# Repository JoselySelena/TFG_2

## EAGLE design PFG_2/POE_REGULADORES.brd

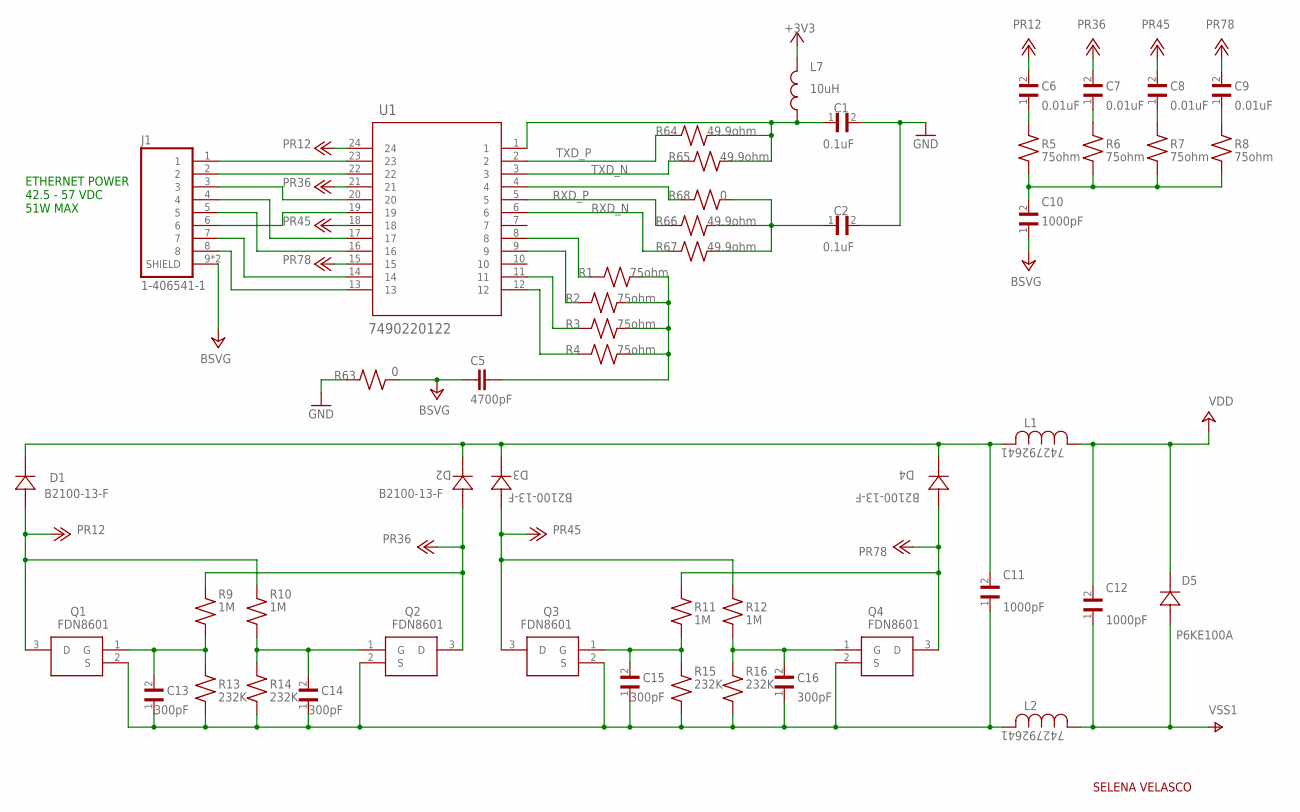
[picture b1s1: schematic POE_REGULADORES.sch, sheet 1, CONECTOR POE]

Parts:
C1, C2: 0.1uF; CAPC3316X98N
C5: 4700pF; C4532
C6, C7, C8, C9: 0.01uF; CAPC3316X98N
C10: 1000pF; CAPC4520X150N
C11, C12: 1000pF; CAPC3316X98N
C13, C14, C15, C16: 300pF; CAPC3316X98N
D1, D2, D3, D4: B2100-13-F; SMB_DIO
D5: P6KE100A; P6KESERIES_LTF
J1: 1-406541-1; CONN_1-406541-1
L1, L2: 742792641; IND_742792641_WRE
L7: 10uH; INDM3225X210N
Q1, Q2, Q3, Q4: FDN8601; SOT95P251X112-3N
R1, R2, R3, R4, R5, R6, R7, R8: 75ohm; RESC3116X65N
R9, R10, R11, R12: 1M; RESC3116X65N
R13, R14, R15, R16: 232K; RESC3116X65N
R63, R68: 0; RESC3116X65N
R64, R65, R66, R67: 49.9ohm; RESC3116X65N
U1: 7490220122; 7490220122_WRE

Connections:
+3V3: L7.2; also elsewhere on the board
BSVG: C5.1, C10.1, J1.9 (SHIELD), J1.10 (SHIELD), R63.1
GND: C1.2, C2.2, R63.2; also elsewhere on the board
unnamed: J1.1, U1.23
unnamed: J1.2, U1.22
unnamed: J1.3, U1.20
unnamed: J1.4, U1.17
unnamed: J1.5, U1.16
unnamed: J1.6, U1.19
unnamed: J1.7, U1.14
unnamed: J1.8, U1.13
unnamed: C14.2, Q2.1 (G), R10.1, R14.2
unnamed: C6.1, R5.2
unnamed: C7.1, R6.2
unnamed: C8.1, R7.2
unnamed: C9.1, R8.2
unnamed: C10.2, R5.1, R6.1, R7.1, R8.1
unnamed: R1.1, U1.8
unnamed: C5.2, R1.2, R2.2, R3.2, R4.2
unnamed: R2.1, U1.9
unnamed: R3.1, U1.11
unnamed: R4.1, U1.12
unnamed: C13.2, Q1.1 (G), R9.1, R13.2
unnamed: C15.2, Q3.1 (G), R11.1, R15.2
unnamed: C16.2, Q4.1 (G), R12.1, R16.2
unnamed: C11.2, D1.1, D2.1, D3.1, D4.1, L1.2
unnamed: C11.1, C13.1, C14.1, C15.1, C16.1, L2.2, Q1.2 (S), Q2.2 (S), Q3.2 (S), Q4.2 (S), R13.1, R14.1, R15.1, R16.1
unnamed: R68.1, U1.4
unnamed: C2.1, R66.2, R67.2, R68.2
PR12: C6.2, D1.2, Q1.3 (D), R10.2, U1.24
PR36: C7.2, D2.2, Q2.3 (D), R9.2, U1.21
PR45: C8.2, D3.2, Q3.3 (D), R12.2, U1.18
PR78: C9.2, D4.2, Q4.3 (D), R11.2, U1.15
RXD_N: R67.1, U1.6; also elsewhere on the board
RXD_P: R66.1, U1.5; also elsewhere on the board
TXD_CT: C1.1, L7.1, R64.2, R65.2, U1.1
TXD_N: R65.1, U1.3; also elsewhere on the board
TXD_P: R64.1, U1.2; also elsewhere on the board
VDD: C12.2, D5.1, L1.1; also elsewhere on the board
VSS1: C12.1, D5.2, L2.1; also elsewhere on the board

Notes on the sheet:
ETHERNET POWER 42.5 - 57 VDC 51W MAX
SELENA VELASCO

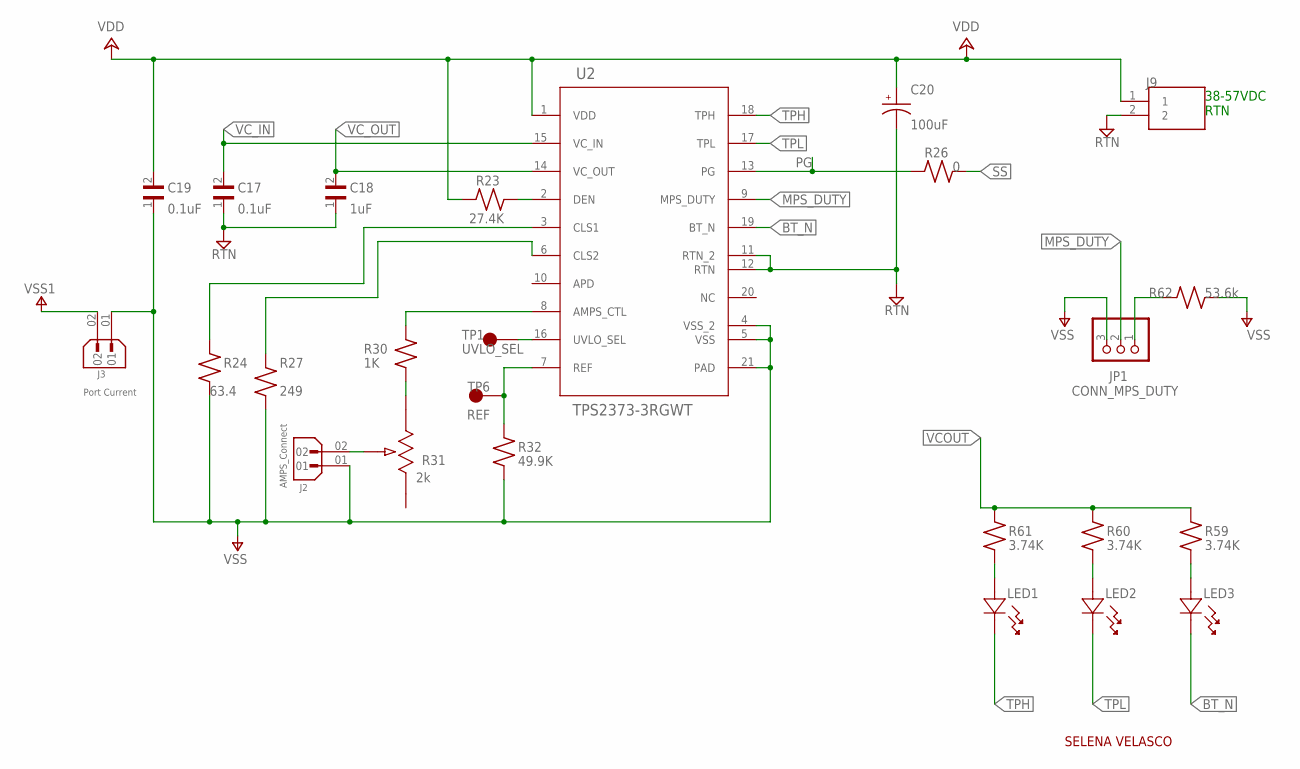
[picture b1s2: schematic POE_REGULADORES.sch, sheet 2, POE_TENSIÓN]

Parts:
C17, C19: 0.1uF; CAPC3316X98N
C18: 1uF; CAPC3316X98N
C20: 100uF; CAP_EEEFK1J470P
J2: AMPS_Connect; WURTH_61300211121
J3: Port Current; WURTH_61300211121
J9: TB001-500-02BE; CUI_TB001-500-02BE
JP1: CONN_MPS_DUTY; 1X03
LED1, LED2, LED3: BL-BGE1V1; BL-BGE1V1_AMB
R23: 27.4K; RESC3116X65N
R24: 63.4; RESC3116X65N
R26: 0; RESC3116X65N
R27: 249; RESC3116X65N
R30: 1K; RESC3116X65N
R31: 2k; POT_3386P
R32: 49.9K; RESC3116X65N
R59, R60, R61: 3.74K; RESC3116X65N
R62: 53.6k; RESC3116X65N
TP1: UVLO_SEL; KEYSTONE_5019
TP6: REF; KEYSTONE_5019
U2: TPS2373-3RGWT; RGW0020B

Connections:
BT_N: LED3.1, U2.19 (BT_N)
MPS_DUTY: JP1.2, U2.9 (MPS_DUTY)
unnamed: LED3.2, R59.1
unnamed: R24.2, U2.3 (CLS1)
unnamed: R27.2, U2.6 (CLS2)
unnamed: R32.2, TP6.TP, U2.7 (REF)
unnamed: R30.1, R31.3
unnamed: J2.02, R31.2
unnamed: R23.2, U2.2 (DEN)
unnamed: R30.2, U2.8 (AMPS_CTL)
unnamed: TP1.TP, U2.16 (UVLO_SEL)
unnamed: JP1.1, R62.2
unnamed: LED1.2, R61.1
unnamed: LED2.2, R60.1
PG: R26.1, U2.13 (PG); also elsewhere on the board
RTN: C17.1, C18.1, C20.2, J9.2, U2.11 (RTN_2), U2.12 (RTN); also elsewhere on the board
SS: R26.2; also elsewhere on the board
TPH: LED1.1, U2.18 (TPH)
TPL: LED2.1, U2.17 (TPL)
VCOUT: R59.2, R60.2, R61.2
VC_IN: C17.2, U2.15 (VC_IN)
VC_OUT: C18.2, U2.14 (VC_OUT)
VDD: C19.2, C20.1, J9.1, R23.1, U2.1 (VDD); also elsewhere on the board
VSS: C19.1, J2.01, J3.01, JP1.3, R24.1, R27.1, R32.1, R62.1, U2.4 (VSS_2), U2.5 (VSS), U2.21 (PAD)
VSS1: J3.02; also elsewhere on the board

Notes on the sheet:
SELENA VELASCO
38-57VDC RTN

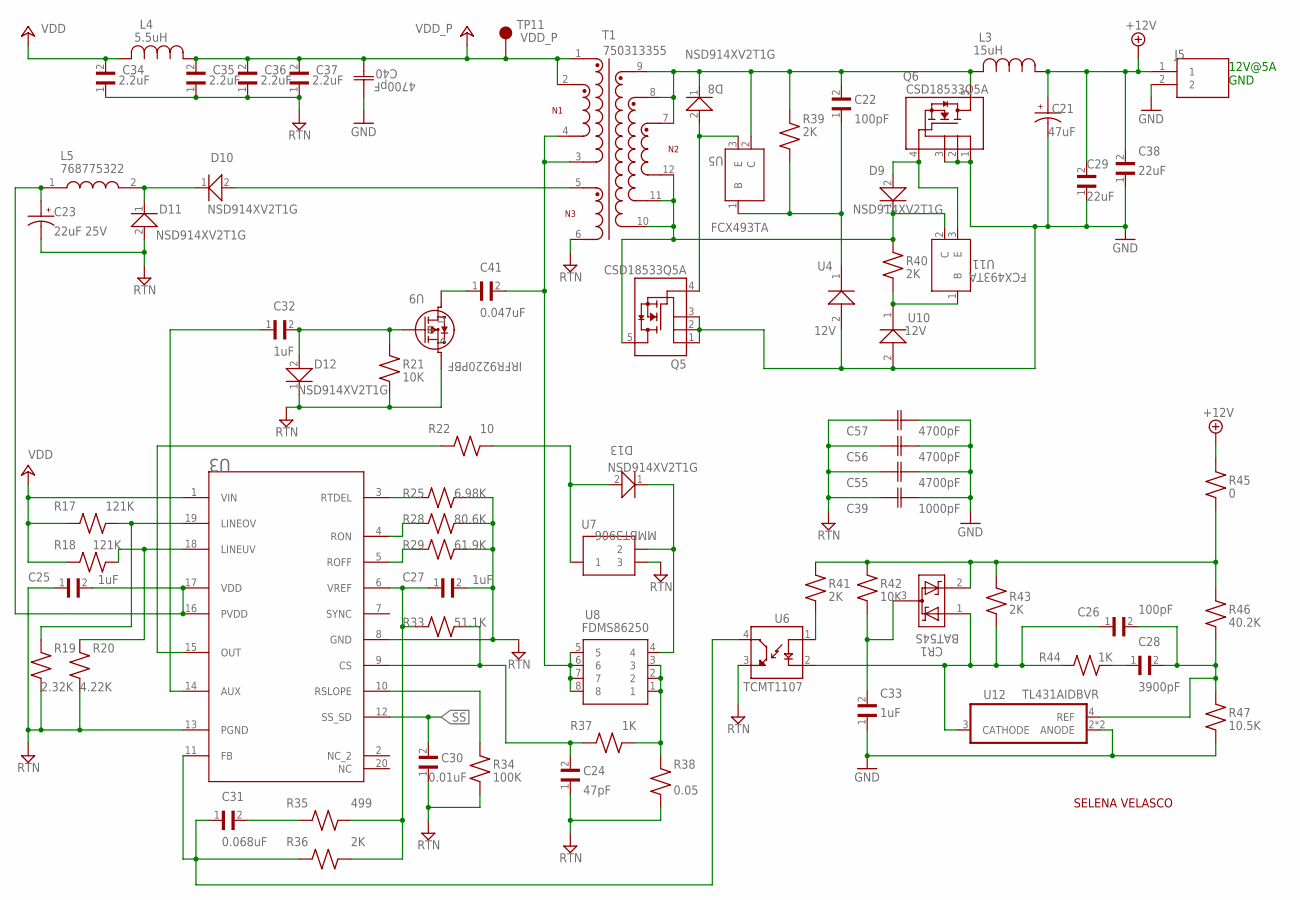
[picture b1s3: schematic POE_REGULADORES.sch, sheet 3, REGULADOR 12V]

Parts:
C21: 47uF; CAP_EEEFK1C470P
C22, C26: 100pF; CAPC3316X98N
C23: 22uF 25V; CAP_EEEFK1E220R
C24: 47pF; CAPC3316X98N
C25, C27, C32, C33: 1uF; CAPC3316X98N
C28: 3900pF; CAPC3316X98N
C29, C38: 22uF; CAPC3316X98N
C30: 0.01uF; CAPC3316X98N
C31: 0.068uF; CAPC3316X98N
C34, C35, C36, C37: 2.2uF; CAPC3316X98N
C39: 1000pF; CAP_1812_AVX
C40, C55, C56, C57: 4700pF; CAP_1812_AVX
C41: 0.047uF; CAPC3316X98N
CR1: BAT54S; SOT-23_TO-236_DTC
D8, D9, D10, D11, D12, D13: NSD914XV2T1G; SOD-523_0P9X1P3_ONS
J5: TB001-500-02BE; CUI_TB001-500-02BE
L3: 15uH; IND_1890_2-WE-HCI_WRE
L4: 5.5uH; IND_1050-WE-HCI_WRE
L5: 768775322
Q5, Q6: CSD18533Q5A; TRANS_CSD18533Q5A
R17, R18: 121K; RESC3116X65N
R19: 2.32K; RESC3116X65N
R20: 4.22K; RESC3116X65N
R21, R42: 10K; RESC3116X65N
R22: 10; RESC3116X65N
R25: 6.98K; RESC3116X65N
R28: 80.6K; RESC3116X65N
R29: 61.9K; RESC3116X65N
R33: 51.1K; RESC3116X65N
R34: 100K; RESC3116X65N
R35: 499; RESC3116X65N
R36, R39, R40, R41, R43: 2K; RESC3116X65N
R37, R44: 1K; RESC3116X65N
R38: 0.05; RESC3116X65N
R45: 0; RESC3116X65N
R46: 40.2K; RESC3116X65N
R47: 10.5K; RESC3116X65N
T1: 750313355; WE-POE++_EFD20_L29.65W21.8H11.43
TP11: VDD_P; KEYSTONE_5019
U3: UCC2897APW; PW0020A
U4, U10: 12V; SOD-123_ONS
U5, U11: FCX493TA; FCX493TA_DIO
U6: TCMT1107; SOIC127P700X230-4N
U7: MMBT3906; SOT-23-3_1P4X3P040_ONS
U8: FDMS86250; FDMS_86250_ONS
U9: IRFR9220PBF; DPAK_VIS
U12: TL431AIDBVR; SOT95P280X145-5N

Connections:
+12V: C21.1, C29.2, C38.2, J5.1, L3.1, R45.2; also elsewhere on the board
AUX: C32.1, U3.14 (AUX)
GND: C21.2, C29.1, C33.1, C38.1, C39.2, C40.1, C55.2, C56.2, C57.2, J5.2, Q5.1 (S_1), Q5.2 (S_2), Q5.3 (S_3), Q6.1 (S_1), Q6.2 (S_2), Q6.3 (S_3), R47.1, U4.2 (ANODE), U10.2 (ANODE), U12.2 (ANODE), U12.5 (ANODE); also elsewhere on the board
unnamed: D10.2 (ANODE), T1.5 (3)
unnamed: D8.2 (ANODE), Q5.4 (G), U5.3 (E)
unnamed: C22.2, D8.1 (CATHODE), L3.2, Q6.5 (D), R39.2, T1.7 (10), T1.8 (11), T1.9 (12), U5.2 (C)
unnamed: D13.2 (ANODE), R22.2, U7.1
unnamed: C26.2, C28.2, R46.1, R47.2, U12.4 (REF)
unnamed: C31.1, R36.1, U3.11 (FB), U6.4 (CT)
unnamed: C31.2, R35.1
unnamed: R41.1, U6.1 (A)
unnamed: R17.2, R19.2, U3.19 (LINEOV)
unnamed: R18.2, R20.2, U3.18 (LINEUV)
unnamed: R25.1, U3.3 (RTDEL)
unnamed: R28.1, U3.4 (RON)
unnamed: R29.1, U3.5 (ROFF)
unnamed: C24.2, R33.2, R37.1, U3.9 (CS)
unnamed: C27.1, R33.1, R35.2, R36.2, U3.6 (VREF)
unnamed: R34.2, U3.10 (RSLOPE)
unnamed: CR1.2 (CATHODE2), R41.2, R42.2, R43.2, R45.1, R46.2
unnamed: C28.1, R44.1
unnamed: R40.1, U10.1 (CATHODE), U11.1 (B)
unnamed: R37.2, R38.2, U8.1, U8.2, U8.3
unnamed: D10.1 (CATHODE), D11.1 (CATHODE), L5.2
unnamed: C32.2, D12.2 (ANODE), R21.2, U9.1 (G)
unnamed: C33.2, CR1.3 (CATHODE1/ANODE2), R42.1
unnamed: C41.2, T1.3 (6), T1.4 (5), U8.5, U8.6, U8.7, U8.8
unnamed: D13.1 (CATHODE), U7.2, U8.4
unnamed: C41.1, U9.2 (D)
unnamed: C26.1, CR1.1 (ANODE1), R43.1, R44.2, U6.2 (C), U12.3 (CATHODE)
unnamed: D9.2 (ANODE), Q6.4 (G), U11.3 (E)
unnamed: C22.1, R39.1, U4.1 (CATHODE), U5.1 (B)
unnamed: D9.1 (CATHODE), Q5.5 (D), R40.2, T1.10 (7), T1.11 (8), T1.12 (9), U11.2 (C)
OUT: R22.1, U3.15 (OUT)
RTN: C23.2, C24.1, C25.1, C27.2, C30.1, C34.1, C35.1, C36.1, C37.1, C39.1, C55.1, C56.1, C57.1, D11.2 (ANODE), D12.1 (CATHODE), R19.1, R20.1, R21.1, R25.2, R28.2, R29.2, R34.1, R38.1, T1.6 (4), U3.8 (GND), U3.13 (PGND), U6.3 (ET), U7.3, U9.3 (S); also elsewhere on the board
SS: C30.2, U3.12 (SS_SD); also elsewhere on the board
VC: C23.1, C25.2, L5.1, U3.16 (PVDD), U3.17 (VDD)
VDD: C34.2, L4.2, R17.1, R18.1, U3.1 (VIN); also elsewhere on the board
VDD_P: C35.2, C36.2, C37.2, C40.2, L4.1, T1.1, T1.2, TP11.TP; also elsewhere on the board

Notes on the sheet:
12V@5A GND
SELENA VELASCO

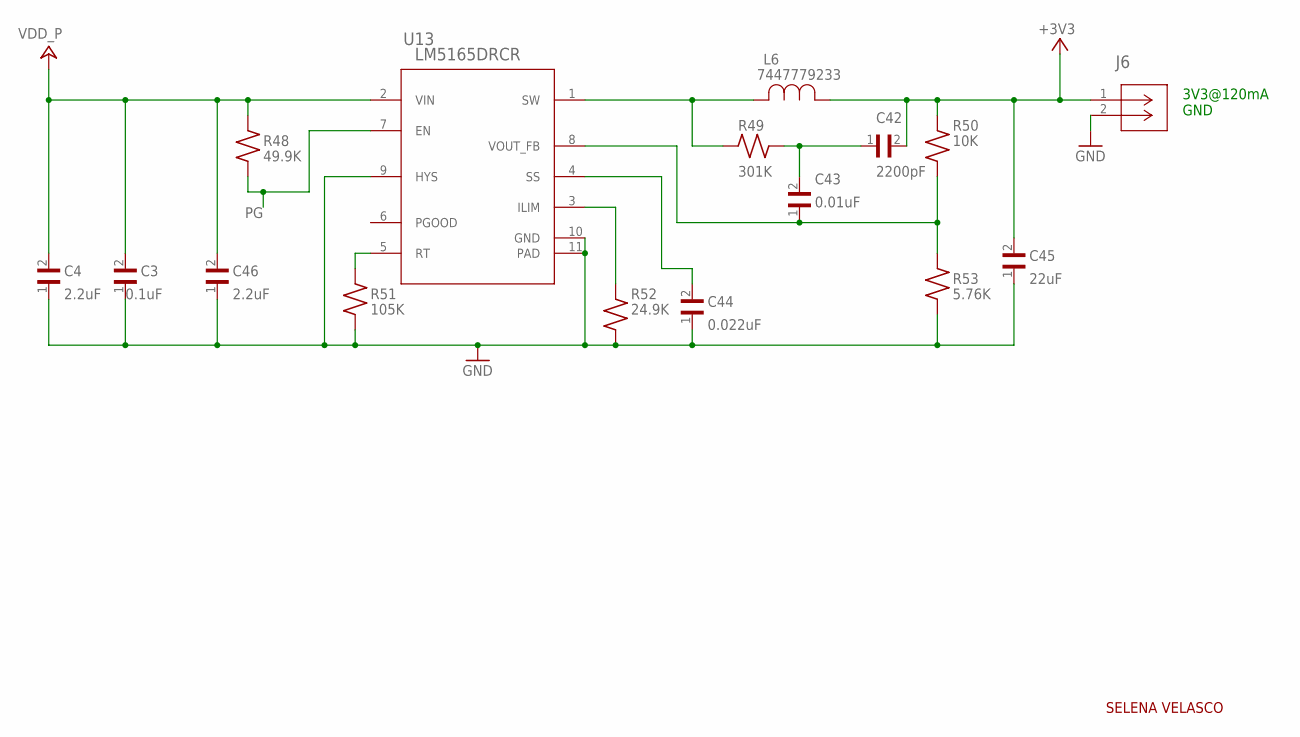
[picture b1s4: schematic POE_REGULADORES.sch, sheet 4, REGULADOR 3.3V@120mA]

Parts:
C3: 0.1uF; CAPC3316X98N
C4, C46: 2.2uF; CAPC3316X98N
C42: 2200pF; CAPC3316X98N
C43: 0.01uF; CAPC3316X98N
C44: 0.022uF; CAPC3316X98N
C45: 22uF; CAPC3316X98N
J6: OSTVN02A150; CONN_OSTVN02A150_OST
L6: 7447779233; IND_7345R_WE-PD_WRE
R48: 49.9K; RESC3116X65N
R49: 301K; RESC3116X65N
R50: 10K; RESC3116X65N
R51: 105K; RESC3116X65N
R52: 24.9K; RESC3116X65N
R53: 5.76K; RESC3116X65N
U13: LM5165DRCR; DRC0010J

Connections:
+3V3: C42.2, C45.2, J6.1, L6.1, R50.2; also elsewhere on the board
GND: C3.1, C4.1, C44.1, C45.1, C46.1, J6.2, R51.1, R52.1, R53.1, U13.9 (HYS), U13.10 (GND), U13.11 (PAD); also elsewhere on the board
unnamed: R51.2, U13.5 (RT)
unnamed: L6.2, R49.1, U13.1 (SW)
unnamed: C42.1, C43.2, R49.2
unnamed: C43.1, R50.1, R53.2, U13.8 (VOUT_FB)
unnamed: C44.2, U13.4 (SS)
unnamed: R52.2, U13.3 (ILIM)
PG: R48.1, U13.7 (EN); also elsewhere on the board
VDD_P: C3.2, C4.2, C46.2, R48.2, U13.2 (VIN); also elsewhere on the board

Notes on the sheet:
3V3@120mA GND
SELENA VELASCO

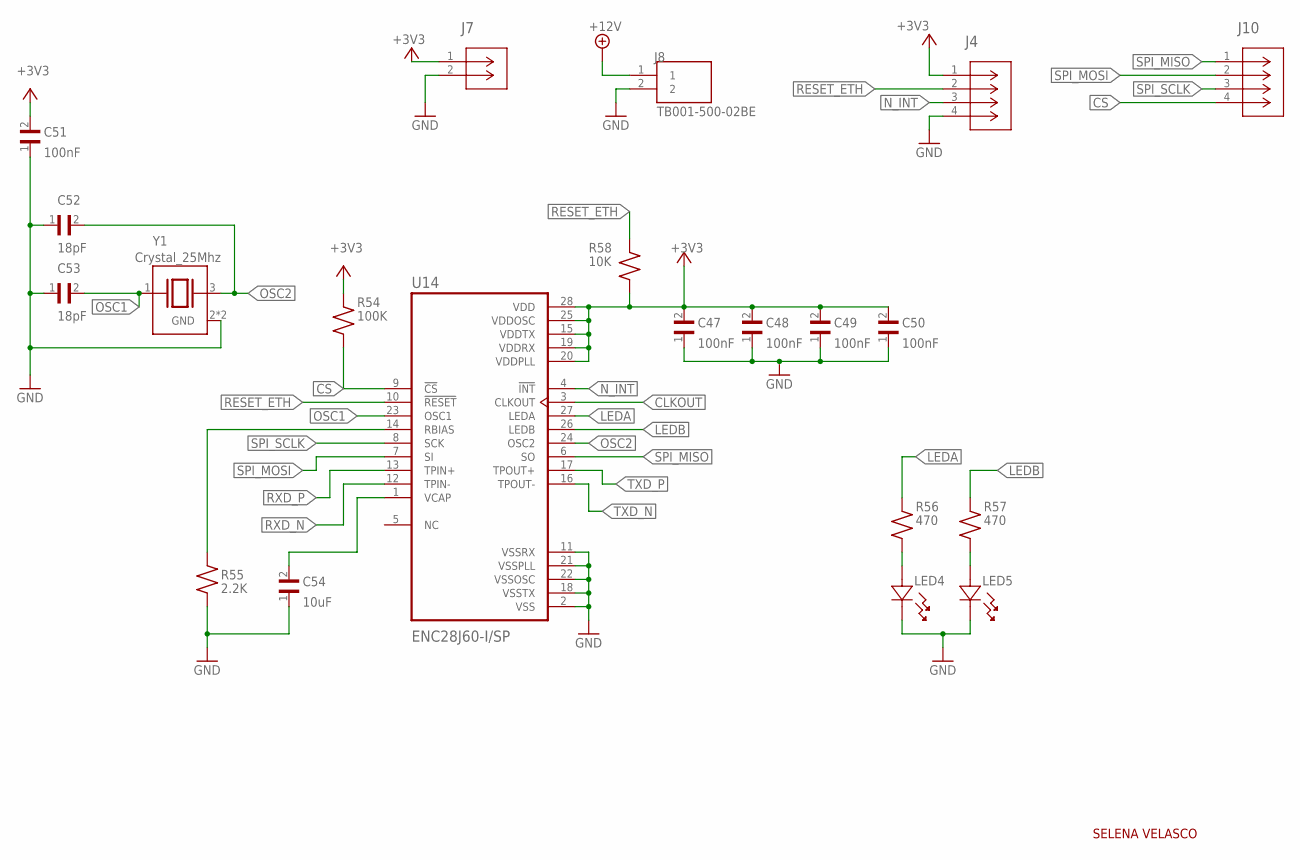
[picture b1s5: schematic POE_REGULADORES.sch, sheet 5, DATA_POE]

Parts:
C47, C48, C49, C50, C51: 100nF; CAPC3316X98N
C52, C53: 18pF; CAPC3316X98N
C54: 10uF; CAPC3316X98N
J4, J10: OSTVN04A150; CONN_OSTVN04A150_OST
J7: OSTVN02A150; CONN_OSTVN02A150_OST
J8: TB001-500-02BE; CUI_TB001-500-02BE
LED4, LED5: BL-BGE1V1; BL-BGE1V1_AMB
R54: 100K; RESC3116X65N
R55: 2.2K; RESC3116X65N
R56, R57: 470; RESC3116X65N
R58: 10K; RESC3116X65N
U14: ENC28J60-I/SP; DIP787W45P254L3556H508Q28
Y1: Crystal_25Mhz; XTAL_TSX-3225_25.0000MF10P-C3

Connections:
+3V3: C47.2, C48.2, C49.2, C50.2, C51.2, J4.1, J7.1, R54.2, R58.1, U14.15 (VDDTX), U14.19 (VDDRX), U14.20 (VDDPLL), U14.25 (VDDOSC), U14.28 (VDD); also elsewhere on the board
+12V: J8.1; also elsewhere on the board
CLKOUT: U14.3 (CLKOUT)
CS: J10.4, R54.1, U14.9 (!CS)
GND: C47.1, C48.1, C49.1, C50.1, C51.1, C52.1, C53.1, C54.1, J4.4, J7.2, J8.2, LED4.1, LED5.1, R55.1, U14.2 (VSS), U14.11 (VSSRX), U14.18 (VSSTX), U14.21 (VSSPLL), U14.22 (VSSOSC), Y1.2 (GND), Y1.4 (GND); also elsewhere on the board
LEDA: R56.2, U14.27 (LEDA)
LEDB: R57.2, U14.26 (LEDB)
unnamed: LED4.2, R56.1
unnamed: C54.2, U14.1 (VCAP)
unnamed: R55.2, U14.14 (RBIAS)
unnamed: LED5.2, R57.1
N_INT: J4.3, U14.4 (!INT)
OSC1: C53.2, U14.23 (OSC1), Y1.1
OSC2: C52.2, U14.24 (OSC2), Y1.3 (2)
RESET_ETH: J4.2, R58.2, U14.10 (!RESET)
RXD_N: U14.12 (TPIN-); also elsewhere on the board
RXD_P: U14.13 (TPIN+); also elsewhere on the board
SPI_MISO: J10.1, U14.6 (SO)
SPI_MOSI: J10.2, U14.7 (SI)
SPI_SCLK: J10.3, U14.8 (SCK)
TXD_N: U14.16 (TPOUT-); also elsewhere on the board
TXD_P: U14.17 (TPOUT+); also elsewhere on the board

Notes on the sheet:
SELENA VELASCO

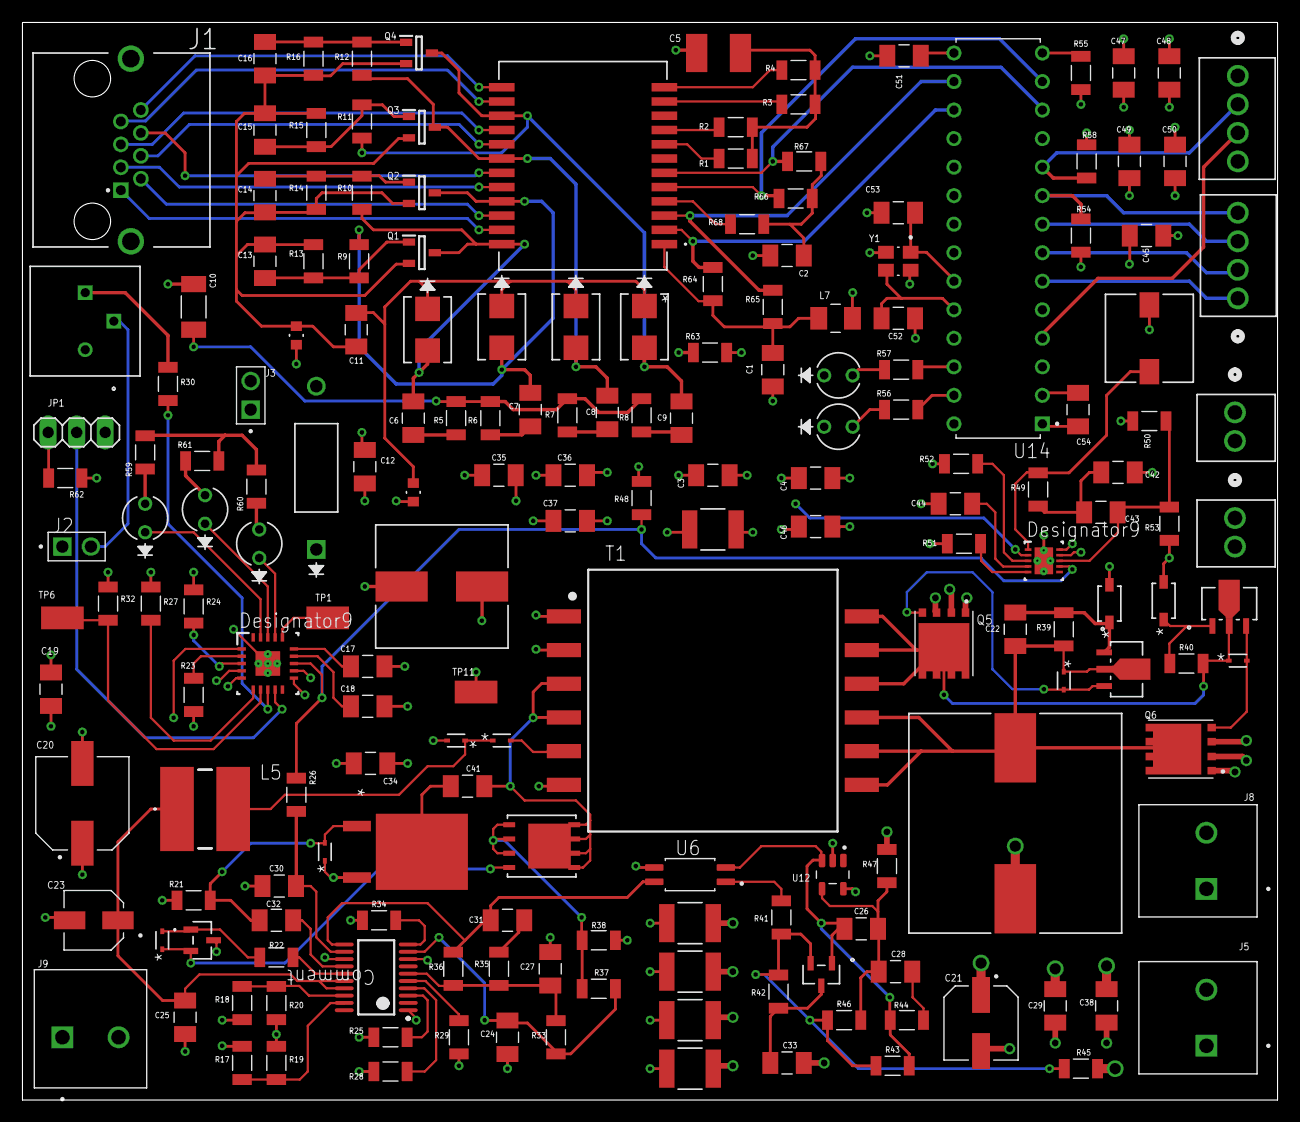
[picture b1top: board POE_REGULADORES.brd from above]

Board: 4 copper layers, 111.7 x 95.9 mm, 185 parts (0 on the bottom side), 118 nets.

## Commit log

2024-05-03 Primera subida, falta colocar POE_reguladores
2024-05-05 Colocados componentes y planos RTN, GND, VDD, VSS, 3V3, 12V
2024-05-06 Colocadas pistas de zona 3V3
2024-05-06 Colocadas vias GND y RTN
2024-05-06 Colocadas vias GND, RTN en cada componente, redistribución de componentes 12V
2024-05-07 Planos de masa y alimentación conectados a los componentes con vias
2024-05-07 Falta vias de conector poe y transformador TPS23
2024-05-09 Finalizado el enrutado y resueltos errores DCR

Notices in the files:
parts and their libraries:
750313355: Copyright: Würth Elektronik
COPYRIGHT: Copyright (C) 2024 Ultra Librarian. All rights reserved.
